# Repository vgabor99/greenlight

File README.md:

# Greenlight

*"And if you gaze long into a screen, the screen also gazes into you."<br>
&nbsp;&nbsp;&nbsp;&nbsp;&nbsp;— Friedrich Nietzsche*

Greenlight is a battery-powered display that tells you whether the house is ready to be armed and left. Mounted
next to the alarm panel at the entrance, it lists anything that needs attention first, such as a window or door
left open or a light left on, and shows *All OK* when there is nothing to do.

In what it shows, it is close to a Home Assistant dashboard. The difference is that it runs on a battery, with a
target of one charge a year or less, so both the hardware and the software are designed around power use:

- **Hardware:** an e-paper panel keeps its image without power, so a screen costs nothing to keep showing.
- **Software:** a screen nobody is looking at doesn't need to be up to date. Greenlight spends most of its life in
  deep sleep and is awake only for the short periods when someone is in sight of it. As soon as nobody is
  watching, it goes back to sleep.

## Parts

- Hardware: an ESP32-C6 microcontroller, a 4.2" 400x300 e-paper display, a low-power PIR sensor, a pair button,
  and a few resistors and capacitors. A custom PCB holds them together in a 3D-printed enclosure. Details:
  [docs/hardware.md](docs/hardware.md).
- Firmware: ESP-IDF v6.1 (C, CMake), a Zigbee sleepy end device.
- Home Assistant side: Zigbee2MQTT with the external converter in `z2m/`, templates and an automation in `ha/`.

## Status

Works end to end on a breadboard, with real deep sleep and real battery and USB sensing. The PCB is designed but
not built yet. Details: [docs/roadmap.md](docs/roadmap.md).

## Repository layout

```
main/        firmware, grouped by concern: app/, board/, display/, panel/, screen/, zigbee/, util/
hardware/    KiCad 10 schematic and PCB, project libraries (lib/), board outline DXF (mechanical/)
tools/       bitmap and mockup generators, serial console, framebuffer dump, Zigbee bench test, docs checker
z2m/         Zigbee2MQTT external converter
ha/          Home Assistant templates and package
docs/        design, history, roadmap and research notes, UI spec and mockups (start at docs/README.md)
.claude/     Claude Code skills: bench testing, HA deploy, panel troubleshooting, bitmaps, docs check, KiCad
CLAUDE.md    build environment and conventions
```

## Building

### Before you start

This is a personal project tailored to my own needs, development environment, and home.

`CLAUDE.md` and the skills in `.claude/` describe my setup. Serial ports, installation paths, the MQTT broker's address,
and Home Assistant entity names all belong to one particular home. Change them to match yours. Development and testing
work best when an AI agent has access to your Home Assistant instance and MQTT broker.

The code and documentation are in English, but because the project was built for a Hungarian home,
you'll find a bit of Hungarian here and there, mostly in the screen texts
([docs/uispec/ui-spec.md](docs/uispec/ui-spec.md)). If you feel like learning Hungarian, godspeed!

### Firmware build and flash

You need ESP-IDF v6.1 and a Seeed XIAO ESP32-C6. Activate ESP-IDF ([CLAUDE.md](CLAUDE.md) shows how on my Windows and
Mac machines), then run:

```
idf.py build
idf.py -p <port> flash
```

### Zigbee2MQTT

Load `z2m/greenlight.mjs` into Zigbee2MQTT as an external converter
([docs/zigbee.md](docs/zigbee.md#external-converter)).

### Home Assistant

Copy the template from `ha/custom_templates/` and the package from `ha/packages/` into the same folders of your Home
Assistant configuration ([docs/home-assistant.md](docs/home-assistant.md)).

### Testing

The bench test (`tools/paced_write_test.py`) talks to the MQTT broker, so its MQTT user needs read access to the bridge
and read-write access to the device. For example, in a Mosquitto `acl_file`:

```
user claude
topic read zigbee2mqtt/bridge/#
topic read zigbee2mqtt/gf_lobby_greenlight/#
topic write zigbee2mqtt/gf_lobby_greenlight/set
```

Before running the test, disable the `Greenlight push` automation
([docs/home-assistant.md](docs/home-assistant.md#push-automation)) so that real data does not interfere with it.

## Documentation

[docs/README.md](docs/README.md) is the index: architecture, device behaviour, data model, Zigbee interface,
Home Assistant side, display, hardware, firmware layout, history and roadmap.

## License

- Firmware, tools, and the Home Assistant and Zigbee2MQTT files: [MIT](LICENSE).
- Hardware (`hardware/`): [CERN-OHL-P-2.0](hardware/LICENSE). Exception: the Seeed Studio XIAO library files in
  `hardware/lib/` and the parts derived from them are CC BY-SA 4.0 ([hardware/lib/README.md](hardware/lib/README.md)).
- Documentation and mockup images (`docs/`): [CC BY 4.0](docs/LICENSE).

Fonts, icons and libraries by others: [THIRD_PARTY_NOTICES.md](THIRD_PARTY_NOTICES.md).

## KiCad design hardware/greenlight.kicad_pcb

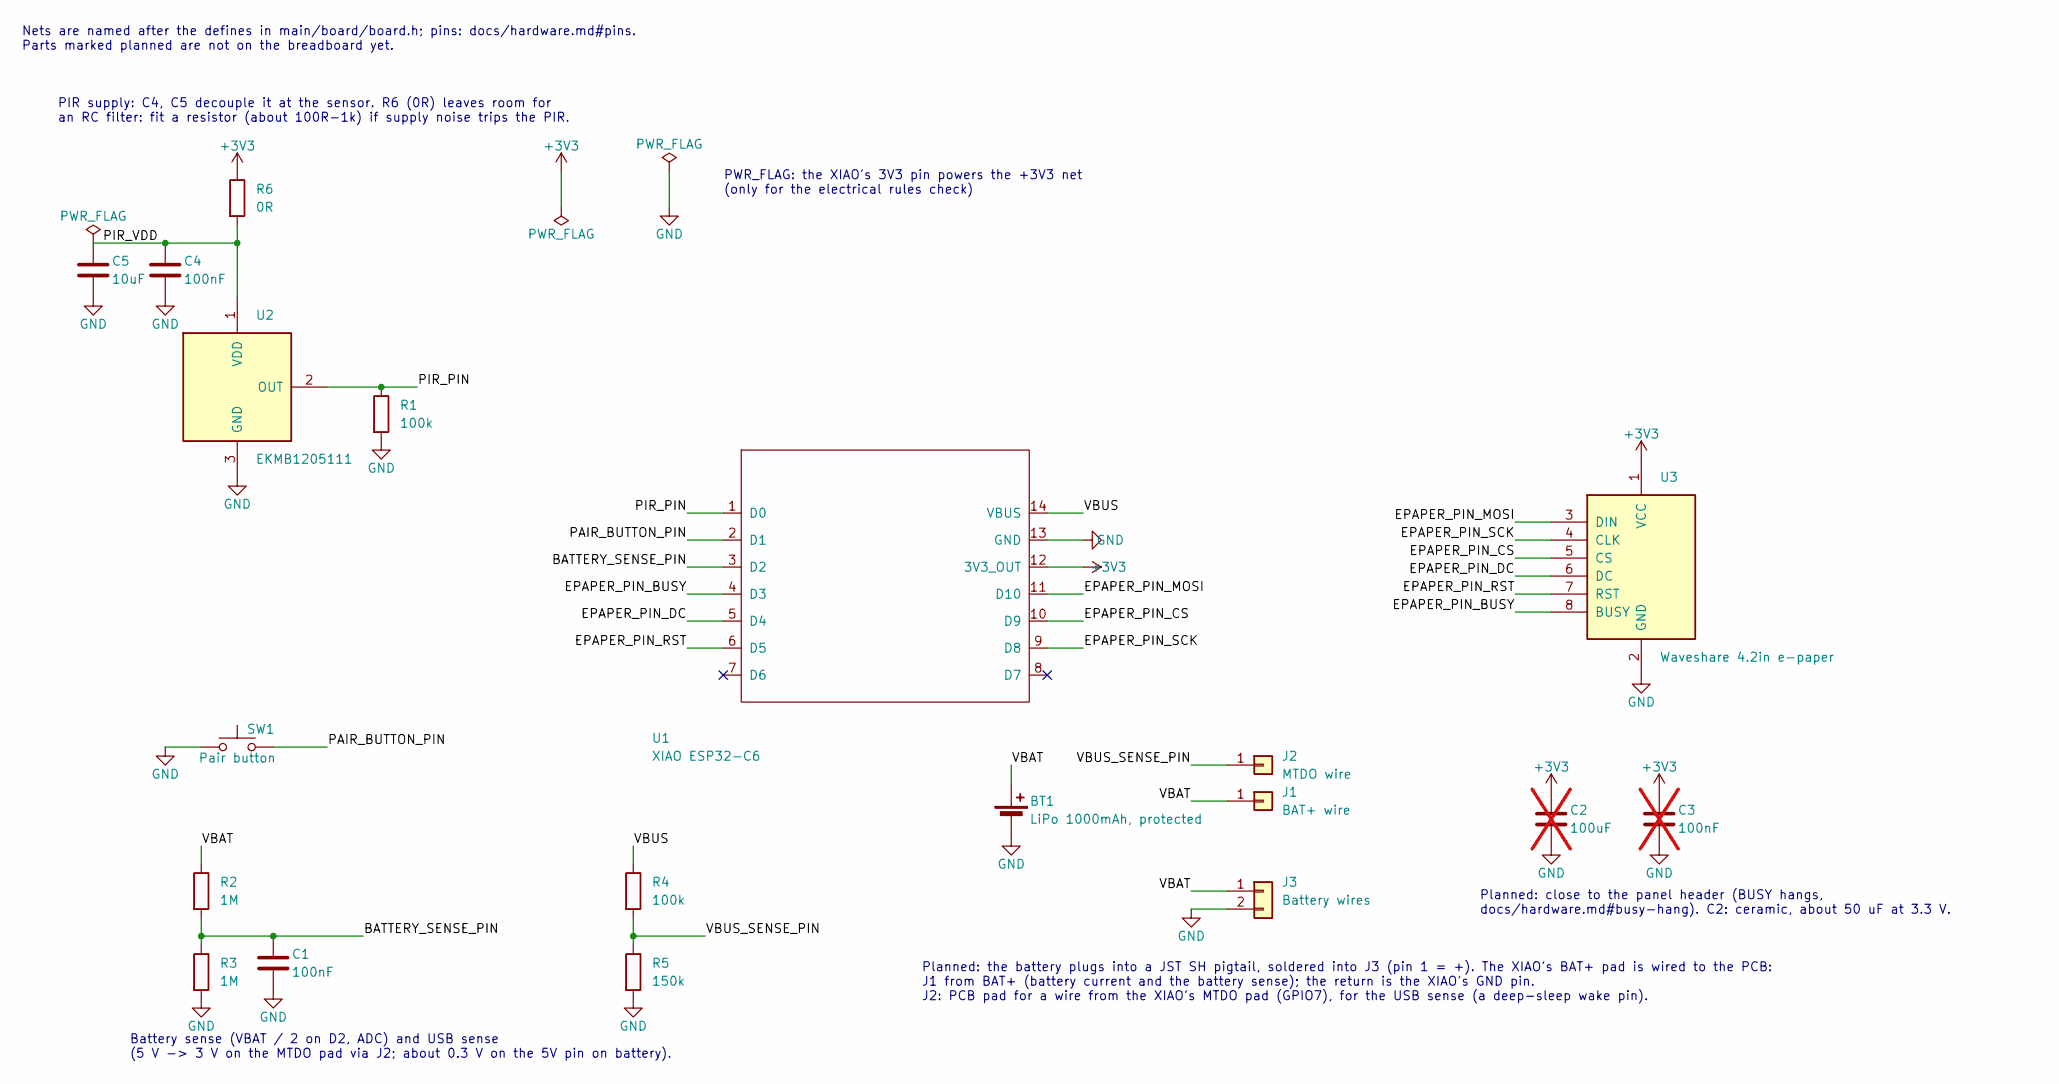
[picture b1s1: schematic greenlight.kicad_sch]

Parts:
BT1: LiPo 1000mAh, protected
C1, C4: 100nF; C_0603_1608Metric; LCSC C14663
C2: 100uF; C_1206_3216Metric; LCSC C15008; not fitted
C3: 100nF; C_0603_1608Metric; LCSC C14663; not fitted
C5: 10uF; C_0603_1608Metric; LCSC C19702
J1: BAT+ wire; TestPoint_THTPad_D2.0mm_Drill1.0mm
J2: MTDO wire; TestPoint_THTPad_D2.0mm_Drill1.0mm
J3: Battery wires; PinHeader_1x02_P2.54mm_Vertical
R1, R4: 100k; R_0603_1608Metric; LCSC C25803
R2, R3: 1M; R_0603_1608Metric; LCSC C22935
R5: 150k; R_0603_1608Metric; LCSC C22807
R6: 0R; R_0603_1608Metric; LCSC C21189
SW1: Pair button; SW_Tactile_SPST_Angled_PTS645Vx31-2LFS
U1: XIAO ESP32-C6; XIAO-ESP32-C6-Header
U2: EKMB1205111; PIR_Panasonic_EKMB_TO5
U3: Waveshare 4.2in e-paper; Panel_Wires_1x08

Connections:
+3V3: C2.1, C3.1, R6.1, U1.12 (3V3_OUT), U3.1 (VCC)
/BATTERY_SENSE_PIN: C1.1, R2.2, R3.1, U1.3 (D2)
/EPAPER_PIN_BUSY: U1.4 (D3), U3.8 (BUSY)
/EPAPER_PIN_CS: U1.10 (D9), U3.5 (CS)
/EPAPER_PIN_DC: U1.5 (D4), U3.6 (DC)
/EPAPER_PIN_MOSI: U1.11 (D10), U3.3 (DIN)
/EPAPER_PIN_RST: U1.6 (D5), U3.7 (RST)
/EPAPER_PIN_SCK: U1.9 (D8), U3.4 (CLK)
/PAIR_BUTTON_PIN: SW1.2 (2_2), U1.2 (D1)
/PIR_PIN: R1.1, U1.1 (D0), U2.2 (OUT)
/PIR_VDD: C4.1, C5.1, R6.2, U2.1 (VDD)
/VBAT: BT1.1 (+), J1.1 (Pin_1_1), J3.1, R2.1
/VBUS: R4.1, U1.14 (VBUS)
/VBUS_SENSE_PIN: J2.1 (Pin_1_1), R4.2, R5.1
GND: BT1.2 (-), C1.2, C2.2, C3.2, C4.2, C5.2, J3.2, R1.2, R3.2, R5.2, SW1.1, U1.13 (GND), U2.3 (GND), U3.2 (GND)

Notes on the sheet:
Planned: close to the panel header (BUSY hangs, docs/hardware.md#busy-hang). C2: ceramic, about 50 uF at 3.3 V.
Planned: the battery plugs into a JST SH pigtail, soldered into J3 (pin 1 = +). The XIAO's BAT+ pad is wired to the PCB: J1 from BAT+ (battery current and the battery sense); the return is the XIAO's GND pin. J2: PCB pad for a wire from the XIAO's MTDO pad (GPIO7), for the USB sense (a deep-sleep w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
Battery sense (VBAT / 2 on D2, ADC) and USB sense (5 V -> 3 V on the MTDO pad via J2; about 0.3 V on the 5V pin on battery).
PWR_FLAG: the XIAO's 3V3 pin powers the +3V3 net (only for the electrical rules check)
Nets are named after the defines in main/board/board.h; pins: docs/hardware.md#pins. Parts marked planned are not on the breadboard yet.
PIR supply: C4, C5 decouple it at the sensor. R6 (0R) leaves room for an RC filter: fit a resistor (about 100R-1k) if supply noise trips the PIR.

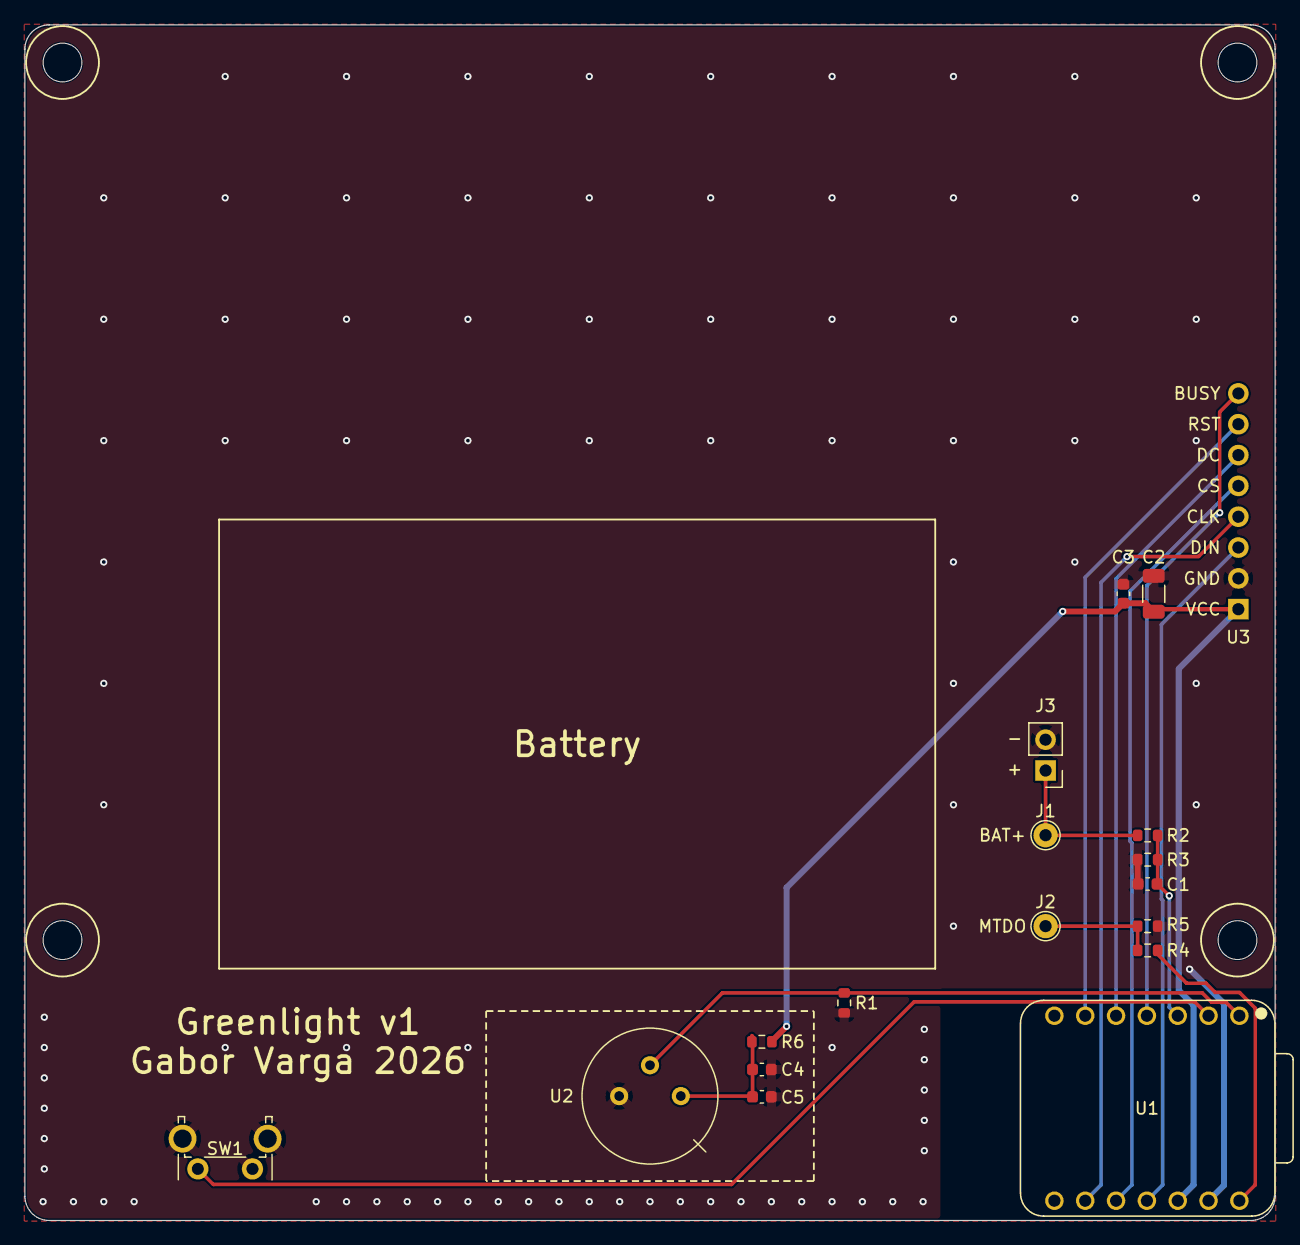
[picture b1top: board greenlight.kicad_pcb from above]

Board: 2 copper layers, 103.0 x 98.5 mm, 22 parts (0 on the bottom side), 15 nets.

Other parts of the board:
H1, H2, H3, H4: MountingHole_3.2mm_M3

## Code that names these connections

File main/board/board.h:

#pragma once

/* Pin assignment: GPIO numbers on a Seeed XIAO ESP32-C6 (D-label in comment) */

/* The e-paper panel (epaper.c) */
#define EPAPER_PIN_SCK  19  /* D8 */
#define EPAPER_PIN_MOSI 18  /* D10 */
#define EPAPER_PIN_CS   20  /* D9 */
#define EPAPER_PIN_DC   22  /* D4 */
#define EPAPER_PIN_RST  23  /* D5 */
#define EPAPER_PIN_BUSY 21  /* D3 */

/* The enclosure mounts the panel upside down: epaper.c rotates the image by 180 degrees in the controller. */
#define PANEL_ROTATED_180 1

/* "Somebody is around" input: Panasonic EKMB PIR output (active high, floats when idle; external 100k
 * pull-down to GND, which keeps the output current under the sensor's 100 uA). Set PIR_ACTIVE_LEVEL to 0
 * for a push button to GND instead: the pin then gets the internal pull-up. Deep-sleep wake pin. */
#define PIR_PIN          0   /* D0 */
#define PIR_ACTIVE_LEVEL 1

/* Pair button between this pin and GND (internal pull-up, active low); deep-sleep wake pin (GPIO0-7) */
#define PAIR_BUTTON_PIN          1  /* D1 */
#define PAIR_BUTTON_ACTIVE_LEVEL 0

/* Battery measurement: VBAT through two equal resistors (100 nF at the pin), ADC1 (battery_sense.c) */
#define BATTERY_SENSE_PIN 2  /* D2 */

/* USB sense: the 5V pin through a divider (about 3 V on USB, 0 on battery), digital input, no pulls (usb_sense.c) */
#define VBUS_SENSE_PIN 7  /* MTDO pad on the XIAO's underside */

/* Antenna switch: RF_SWITCH_ENABLE_PIN low enables it, RF_ANTENNA_SELECT_PIN low selects the onboard ceramic
 * antenna. */
#define RF_SWITCH_ENABLE_PIN  3
#define RF_ANTENNA_SELECT_PIN 14

/* Route the radio to the onboard antenna. */
void board_init_rf_switch(void);
